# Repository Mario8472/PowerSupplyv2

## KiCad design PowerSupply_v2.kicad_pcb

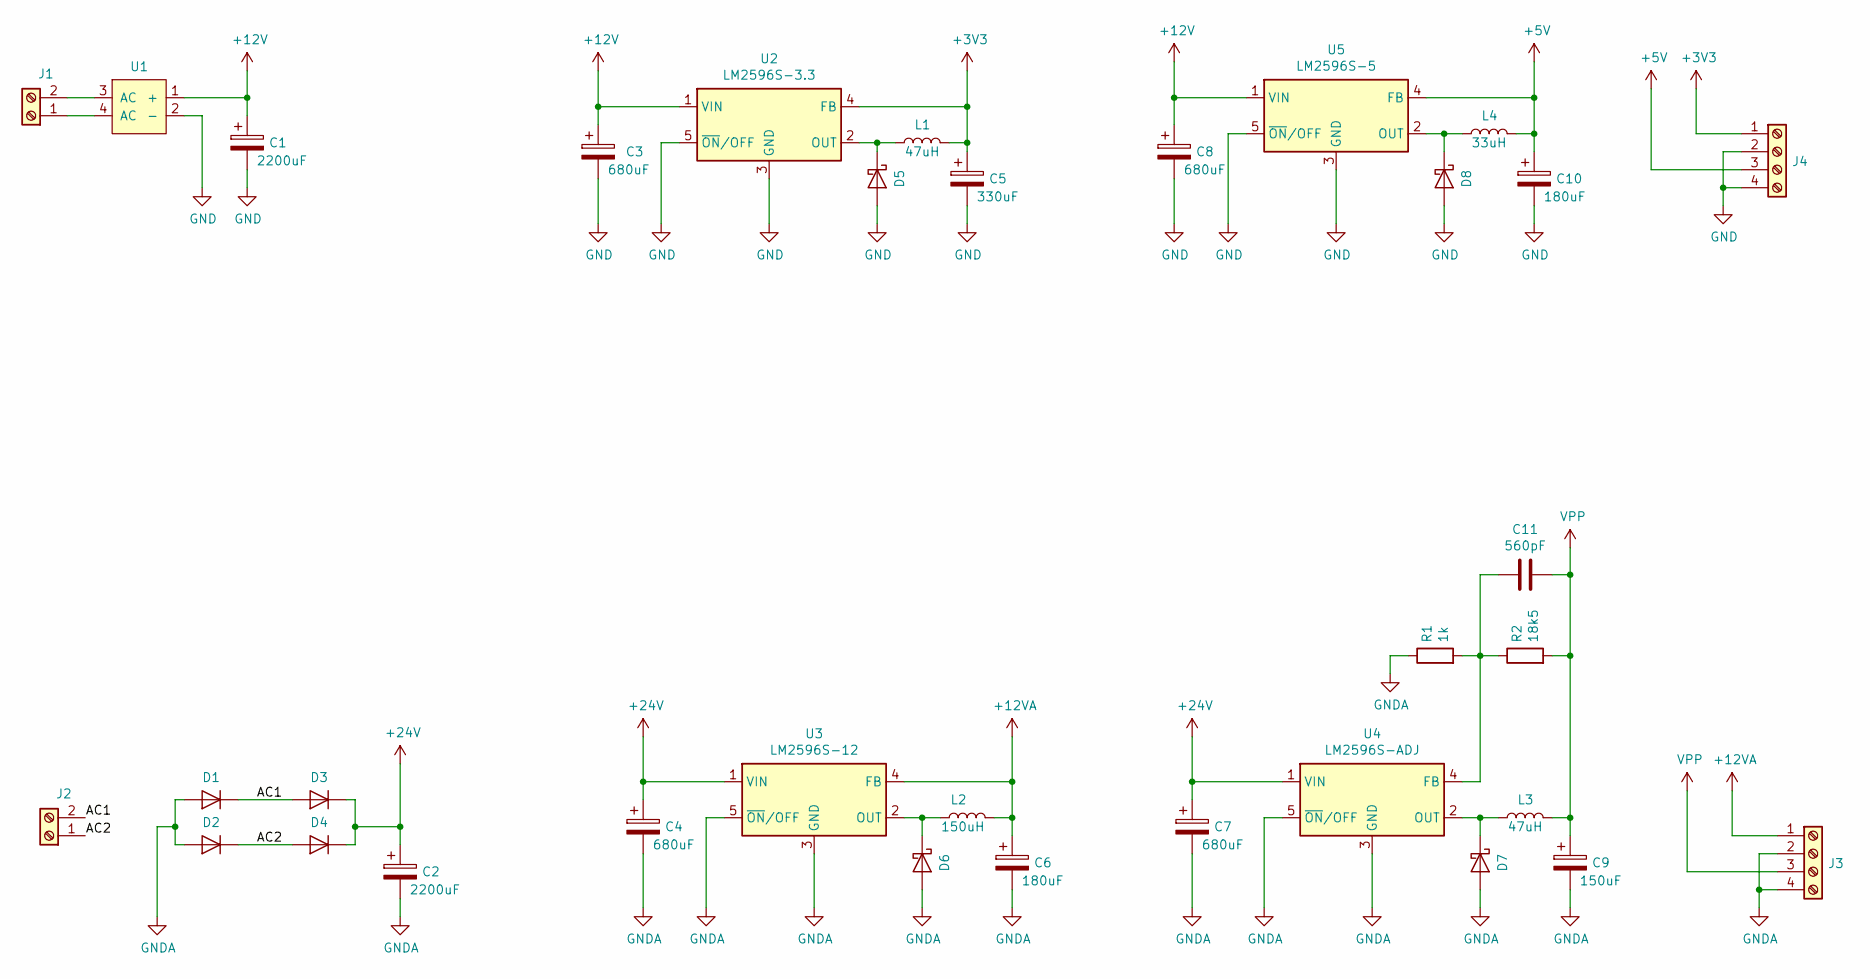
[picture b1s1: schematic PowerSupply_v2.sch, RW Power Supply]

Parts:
C1, C2: 2200uF; CP_Radial_D16.0mm_P7.50mm
C3, C4, C7, C8: 680uF; CP_Radial_D12.5mm_P5.00mm
C5: 330uF; CP_Radial_D8.0mm_P3.50mm
C6, C10: 180uF; CP_Radial_D8.0mm_P3.50mm
C9: 150uF; CP_Radial_D10.0mm_P5.00mm
C11: 560pF; C_0805_2012Metric
D1, D2, D3, D4: D; D_SMC
D5, D6, D7, D8: D_Schottky; D_DO-201AD_P12.70mm_Horizontal
J1, J2: Screw_Terminal_01x02; PCB_Screw_Terminal_5.08_2ways
J3, J4: Screw_Terminal_01x04; PCB_Screw_Terminal_5.08_4ways
L1, L3: 47uH; HPI1206
L2: 150uH; HPI1206
L4: 33uH; HPI1206
R1: 1k; R_0805_2012Metric
R2: 18k5; R_0805_2012Metric
U1: Bridge_Rectifier; DBxxS2
U2: LM2596S-3.3; TO-263-5_TabPin3
U3: LM2596S-12; TO-263-5_TabPin3
U4: LM2596S-ADJ; TO-263-5_TabPin3
U5: LM2596S-5; TO-263-5_TabPin3

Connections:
+3V3: C5.1, J4.1, L1.2, U2.4 (FB)
+5V: C10.1, J4.3, L4.2, U5.4 (FB)
+12V: C1.1, C3.1, C8.1, U1.1 (+), U2.1 (VIN), U5.1 (VIN)
+12VA: C6.1, J3.1, L2.2, U3.4 (FB)
+24V: C2.1, C4.1, C7.1, D3.1 (K), D4.1 (K), U3.1 (VIN), U4.1 (VIN)
/AC1: D1.1 (K), D3.2 (A), J2.2
/AC2: D2.1 (K), D4.2 (A), J2.1
GND: C1.2, C3.2, C5.2, C8.2, C10.2, D5.2 (A), D8.2 (A), J4.2, J4.4, U1.2 (-), U2.3 (GND), U2.5 (~ON~/OFF), U5.3 (GND), U5.5 (~ON~/OFF)
GNDA: C2.2, C4.2, C6.2, C7.2, C9.2, D1.2 (A), D2.2 (A), D6.2 (A), D7.2 (A), J3.2, J3.4, R1.1, U3.3 (GND), U3.5 (~ON~/OFF), U4.3 (GND), U4.5 (~ON~/OFF)
unnamed: C11.2, R1.2, R2.1, U4.4 (FB)
unnamed: D5.1 (K), L1.1, U2.2 (OUT)
unnamed: D6.1 (K), L2.1, U3.2 (OUT)
unnamed: D7.1 (K), L3.1, U4.2 (OUT)
unnamed: D8.1 (K), L4.1, U5.2 (OUT)
unnamed: J1.1, U1.4 (AC)
unnamed: J1.2, U1.3 (AC)
VPP: C9.1, C11.1, J3.3, L3.2, R2.2

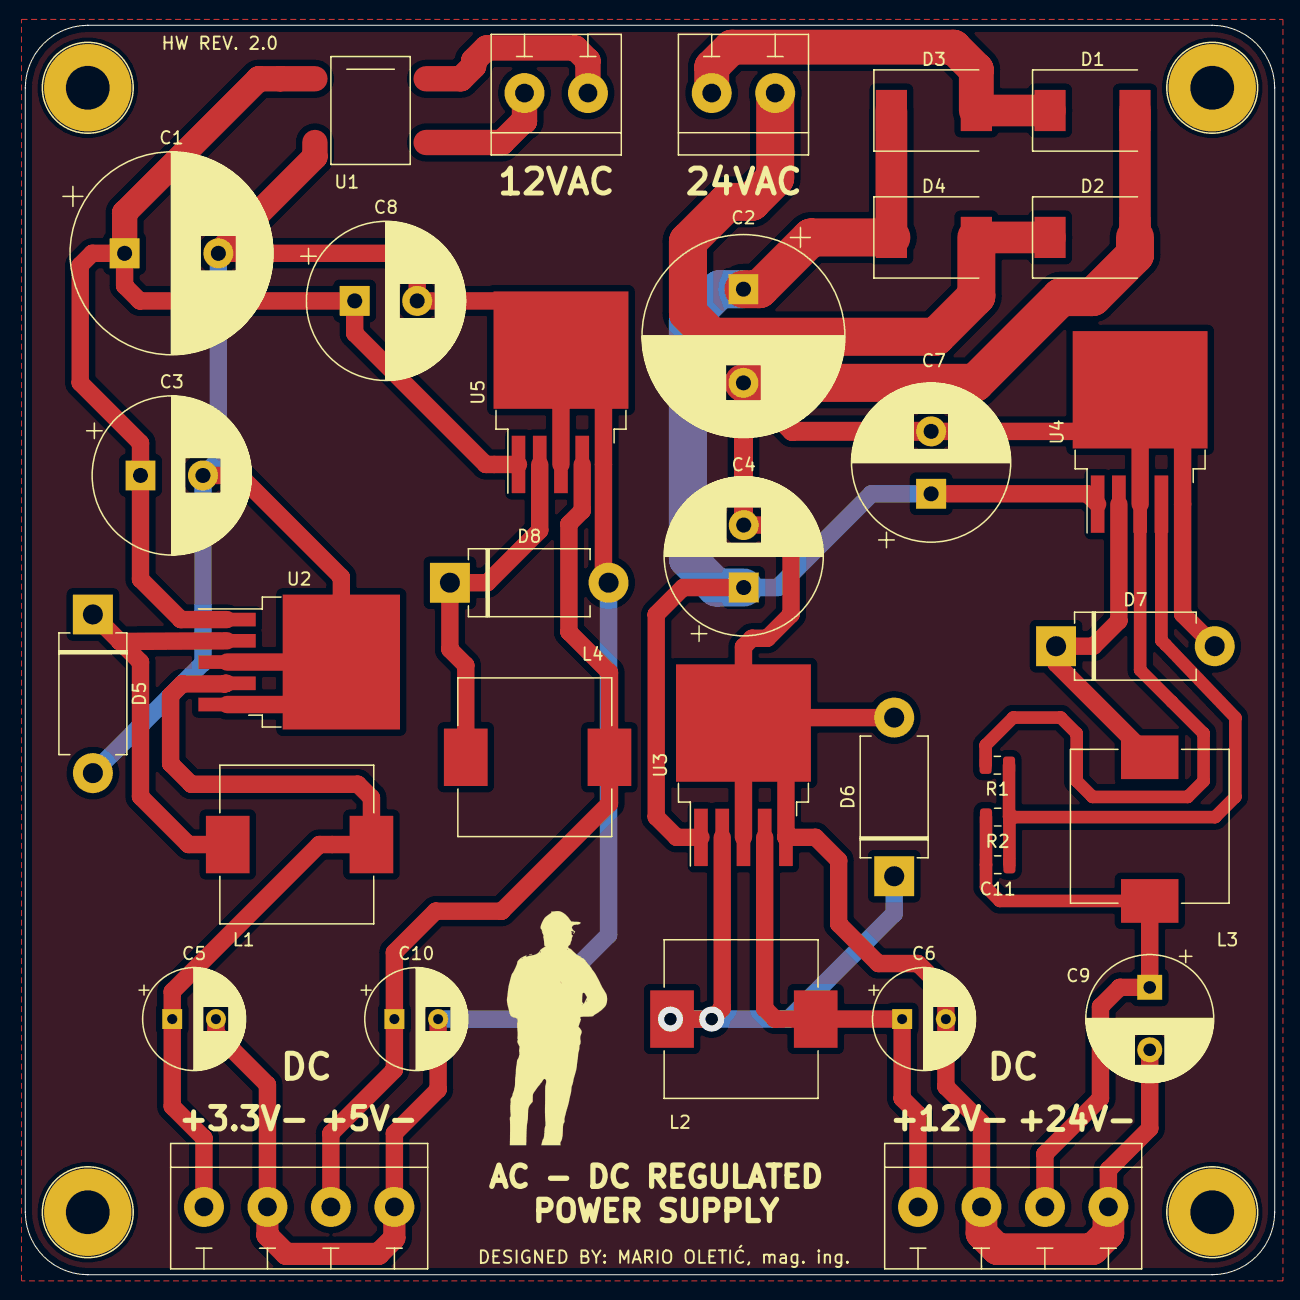
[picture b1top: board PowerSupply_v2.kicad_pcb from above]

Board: 2 copper layers, 100.0 x 100.0 mm, 34 parts (0 on the bottom side), 17 nets.
